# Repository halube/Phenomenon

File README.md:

# Phenomenon - Low-cost and multi-sensor system for automated phenotyping of plant in vitro culture
This is the official code implementation and used hardware of our paper, which is currently under a journal review:

The main mechanical components of the system were:
- OpenBuilds ACRO 1515 60" x 60" (XY gantry)
- Openbuilds Linear Actuator (Z axis)

Network connection & embedded system:
- Router & PoE-Switch
- 2 x Raspberry Pi 4B & PoE-Shield
- 2 x Wemos D1 Mini

Sensors of the system:
- RGB Raspberry Pi Camera High quality 12 MB with Edmund Optics 6mm low distortion lens equipied
- Thermal PureThermal 2 & Lepton 3.5
- Spectral µSpectrometer Hamamatsu C12880MA
- Depth Laser distance sensor OD-Mini OB1-B100

Hardware
- Containing 3D printable parts and PCB-Layouts

Software
- Containing Dockerfiles and Python scripts

Cite:
Bethge H, Winkelmann T, Lüdeke P, Rath T. Low-cost and automated phenotyping system “Phenomenon” for multi-sensor in situ monitoring in plant in vitro culture. Plant methods. 2023 May 2;19(1):42.

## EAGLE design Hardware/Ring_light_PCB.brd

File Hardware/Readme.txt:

Some of the 3D printed parts for cable chain were inspired by the build of "hilleke" & "dragonfire81m" 
(Thingiverse-User: https://www.thingiverse.com/thing:3110642; https://www.thingiverse.com/thing:2780302) but mainly also modified.

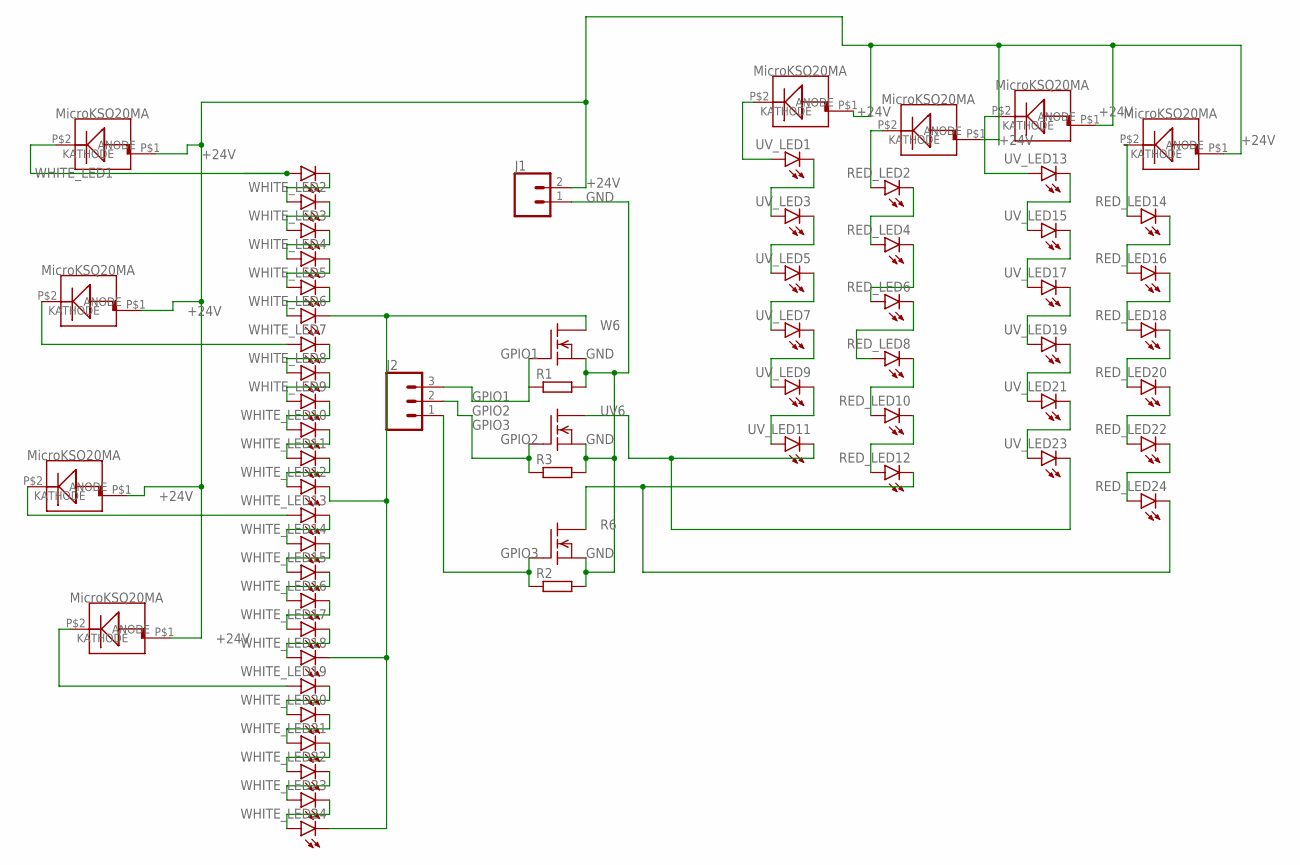
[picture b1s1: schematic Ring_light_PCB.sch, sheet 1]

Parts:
J1: CONN_025MM; SCREWTERMINAL-5MM-2
J2: CONN_03-SCREW-5MM; SCREWTERMINAL-5MM-3
Q1, Q2, Q4: BUZ10; TO220
R1, R2, R3: R-EU_0204/7; 0204/7
RED_LED2, RED_LED4, RED_LED6, RED_LED8, RED_LED10, RED_LED12, RED_LED14, RED_LED16, RED_LED18, RED_LED20, RED_LED22, RED_LED24: LED5MM
U$1, U$2, U$3, U$4, U$5, U$6, U$7, U$8: MICROKSQ220MA; MICROKSQ20MA
UV_LED1, UV_LED3, UV_LED5, UV_LED7, UV_LED9, UV_LED11, UV_LED13, UV_LED15, UV_LED17, UV_LED19, UV_LED21, UV_LED23: LED5MM
WHITE_LED1, WHITE_LED2, WHITE_LED3, WHITE_LED4, WHITE_LED5, WHITE_LED6, WHITE_LED7, WHITE_LED8, WHITE_LED9, WHITE_LED10, WHITE_LED11, WHITE_LED12, WHITE_LED13, WHITE_LED14, WHITE_LED15, WHITE_LED16, WHITE_LED17, WHITE_LED18, WHITE_LED19, WHITE_LED20, WHITE_LED21, WHITE_LED22, WHITE_LED23, WHITE_LED24: LED5MM

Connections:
+24V: J1.2, U$1.P$1 (KATHODE), U$2.P$1 (KATHODE), U$3.P$1 (KATHODE), U$4.P$1 (KATHODE), U$5.P$1 (KATHODE), U$6.P$1 (KATHODE), U$7.P$1 (KATHODE), U$8.P$1 (KATHODE)
GND: J1.1, Q1.3 (S), Q2.3 (S), Q4.3 (S), R1.2, R2.2, R3.2
GPIO1: J2.3, Q1.1 (G), R1.1
GPIO2: J2.2, Q2.1 (G), R3.1
GPIO3: J2.1, Q4.1 (G), R2.1
R0: RED_LED2.A, U$8.P$2 (ANODE)
R1: RED_LED2.K (C), RED_LED4.A
R2: RED_LED4.K (C), RED_LED6.A
R3: RED_LED6.K (C), RED_LED8.A
R4: RED_LED8.K (C), RED_LED10.A
R5: RED_LED10.K (C), RED_LED12.A
R6: Q4.2 (D), RED_LED12.K (C), RED_LED24.K (C)
R7: RED_LED14.A, U$6.P$2 (ANODE)
R8: RED_LED14.K (C), RED_LED16.A
R9: RED_LED16.K (C), RED_LED18.A
R10: RED_LED18.K (C), RED_LED20.A
R11: RED_LED20.K (C), RED_LED22.A
R12: RED_LED22.K (C), RED_LED24.A
UV0: U$7.P$2 (ANODE), UV_LED1.A
UV1: UV_LED1.K (C), UV_LED3.A
UV2: UV_LED3.K (C), UV_LED5.A
UV3: UV_LED5.K (C), UV_LED7.A
UV4: UV_LED7.K (C), UV_LED9.A
UV5: UV_LED9.K (C), UV_LED11.A
UV6: Q2.2 (D), UV_LED11.K (C), UV_LED23.K (C)
UV7: U$5.P$2 (ANODE), UV_LED13.A
UV8: UV_LED13.K (C), UV_LED15.A
UV9: UV_LED15.K (C), UV_LED17.A
UV10: UV_LED17.K (C), UV_LED19.A
UV11: UV_LED19.K (C), UV_LED21.A
UV12: UV_LED21.K (C), UV_LED23.A
W0: U$1.P$2 (ANODE), WHITE_LED1.A
W1: WHITE_LED1.K (C), WHITE_LED2.A
W2: WHITE_LED2.K (C), WHITE_LED3.A
W3: WHITE_LED3.K (C), WHITE_LED4.A
W4: WHITE_LED4.K (C), WHITE_LED5.A
W5: WHITE_LED5.K (C), WHITE_LED6.A
W6: Q1.2 (D), WHITE_LED6.K (C), WHITE_LED12.K (C), WHITE_LED18.K (C), WHITE_LED24.K (C)
W7: U$2.P$2 (ANODE), WHITE_LED7.A
W8: WHITE_LED7.K (C), WHITE_LED8.A
W9: WHITE_LED8.K (C), WHITE_LED9.A
W10: WHITE_LED9.K (C), WHITE_LED10.A
W11: WHITE_LED10.K (C), WHITE_LED11.A
W12: WHITE_LED11.K (C), WHITE_LED12.A
W13: U$3.P$2 (ANODE), WHITE_LED13.A
W14: WHITE_LED13.K (C), WHITE_LED14.A
W15: WHITE_LED14.K (C), WHITE_LED15.A
W16: WHITE_LED15.K (C), WHITE_LED16.A
W17: WHITE_LED16.K (C), WHITE_LED17.A
W18: WHITE_LED17.K (C), WHITE_LED18.A
W19: U$4.P$2 (ANODE), WHITE_LED19.A
W20: WHITE_LED19.K (C), WHITE_LED20.A
W21: WHITE_LED20.K (C), WHITE_LED21.A
W22: WHITE_LED21.K (C), WHITE_LED22.A
W23: WHITE_LED22.K (C), WHITE_LED23.A
W24: WHITE_LED23.K (C), WHITE_LED24.A

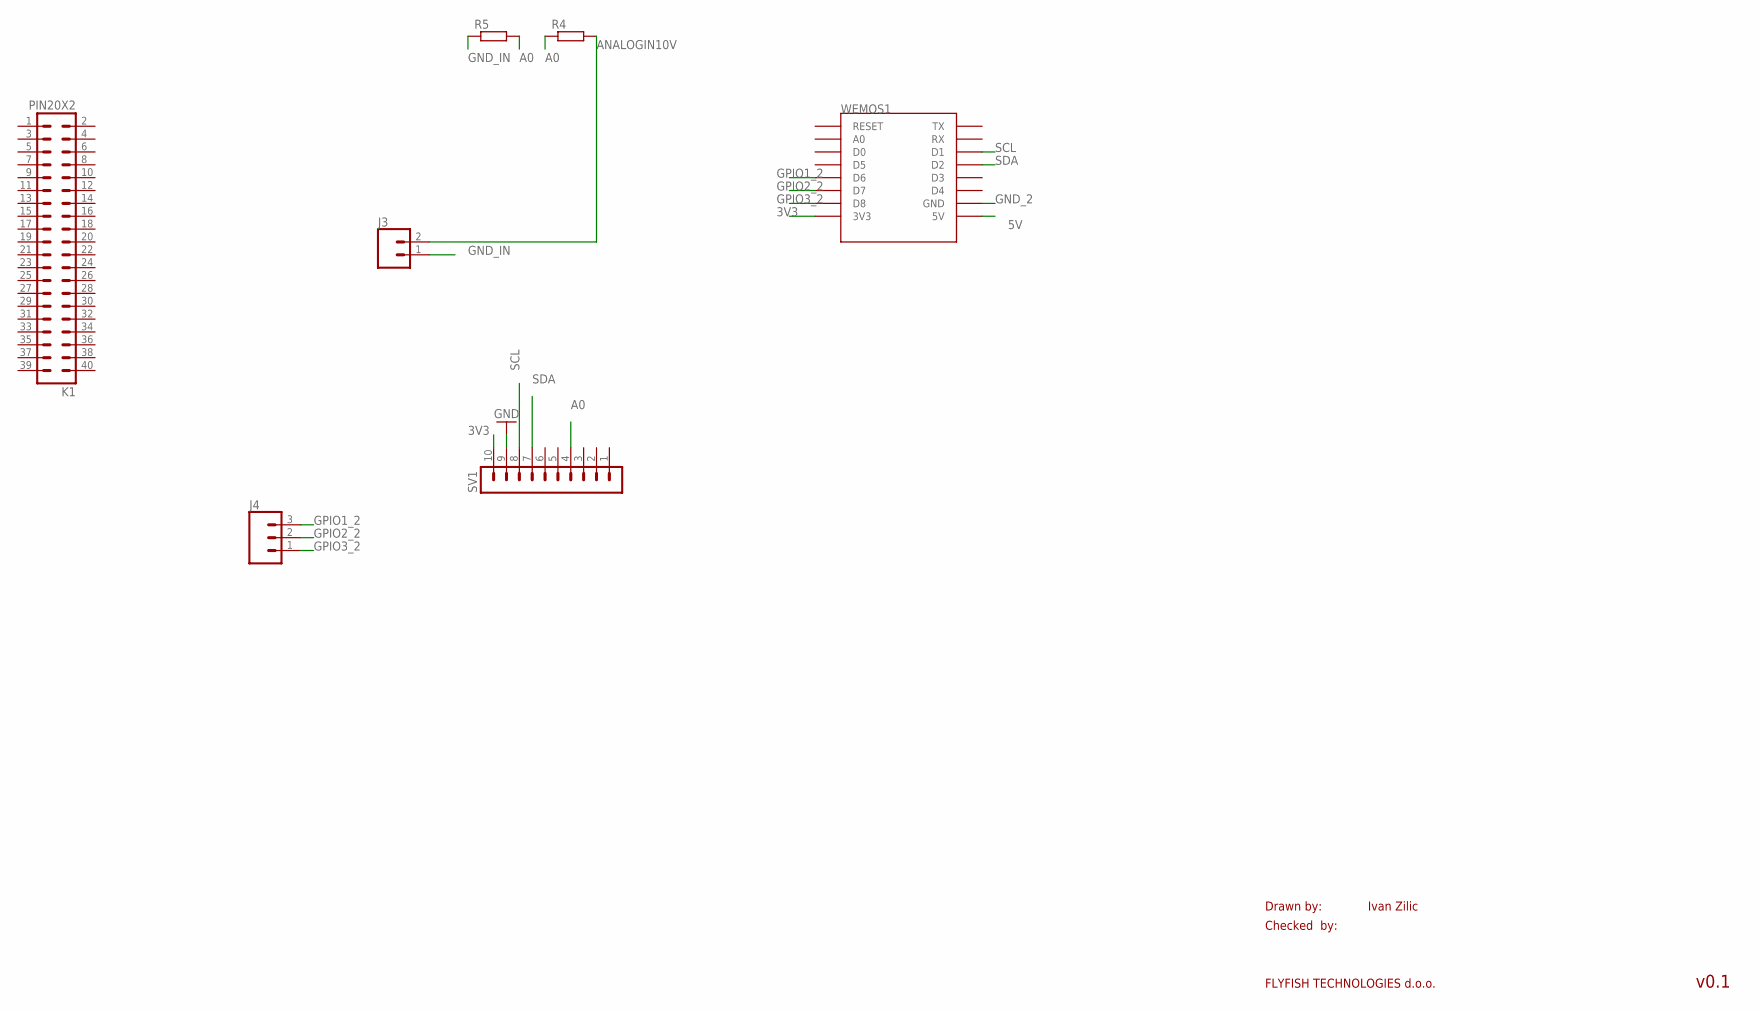
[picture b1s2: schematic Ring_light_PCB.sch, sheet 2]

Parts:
J3: CONN_025MM; SCREWTERMINAL-5MM-2
J4: CONN_03-SCREW-5MM; SCREWTERMINAL-5MM-3
K1: PIN20X2; PIN_20X2
R4, R5: R-EU_0204/7; 0204/7
SV1: MA10-1
WEMOS1: WEMOS-D1-MINI

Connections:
3V3: SV1.10, WEMOS1.3V3
5V: WEMOS1.5V
A0: R4.1, R5.2, SV1.4
ANALOGIN10V: J3.2, R4.2
GND_2: SV1.9, WEMOS1.GND
GND_IN: J3.1, R5.1
GPIO1_2: J4.3, WEMOS1.D6
GPIO2_2: J4.2, WEMOS1.D7
GPIO3_2: J4.1, WEMOS1.D8
SCL: SV1.8, WEMOS1.D1
SDA: SV1.7, WEMOS1.D2

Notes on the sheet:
Drawn by:
Checked by:
FLYFISH TECHNOLOGIES d.o.o.
Ivan Zilic
v0.1

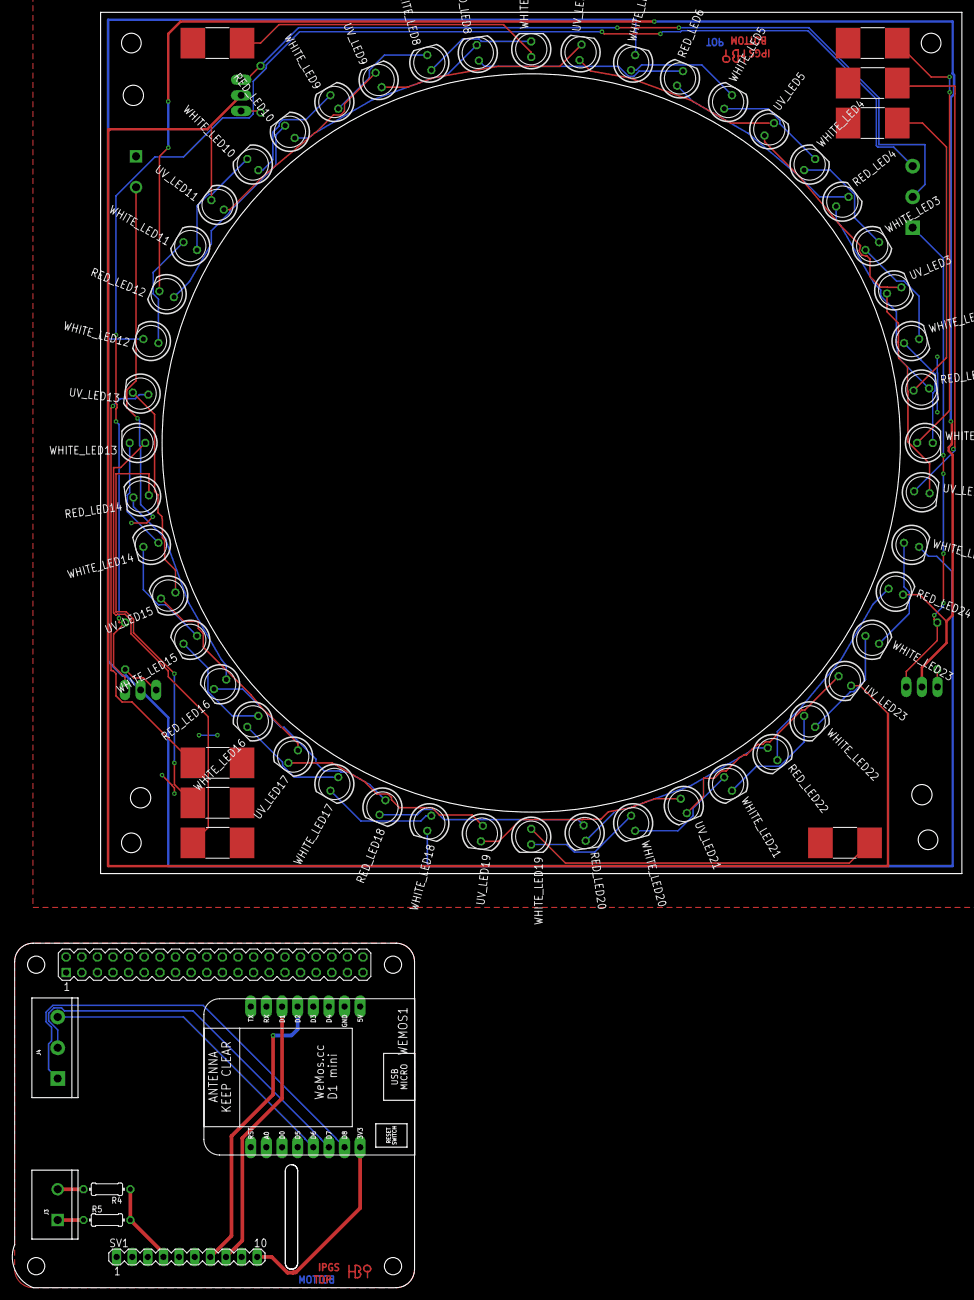
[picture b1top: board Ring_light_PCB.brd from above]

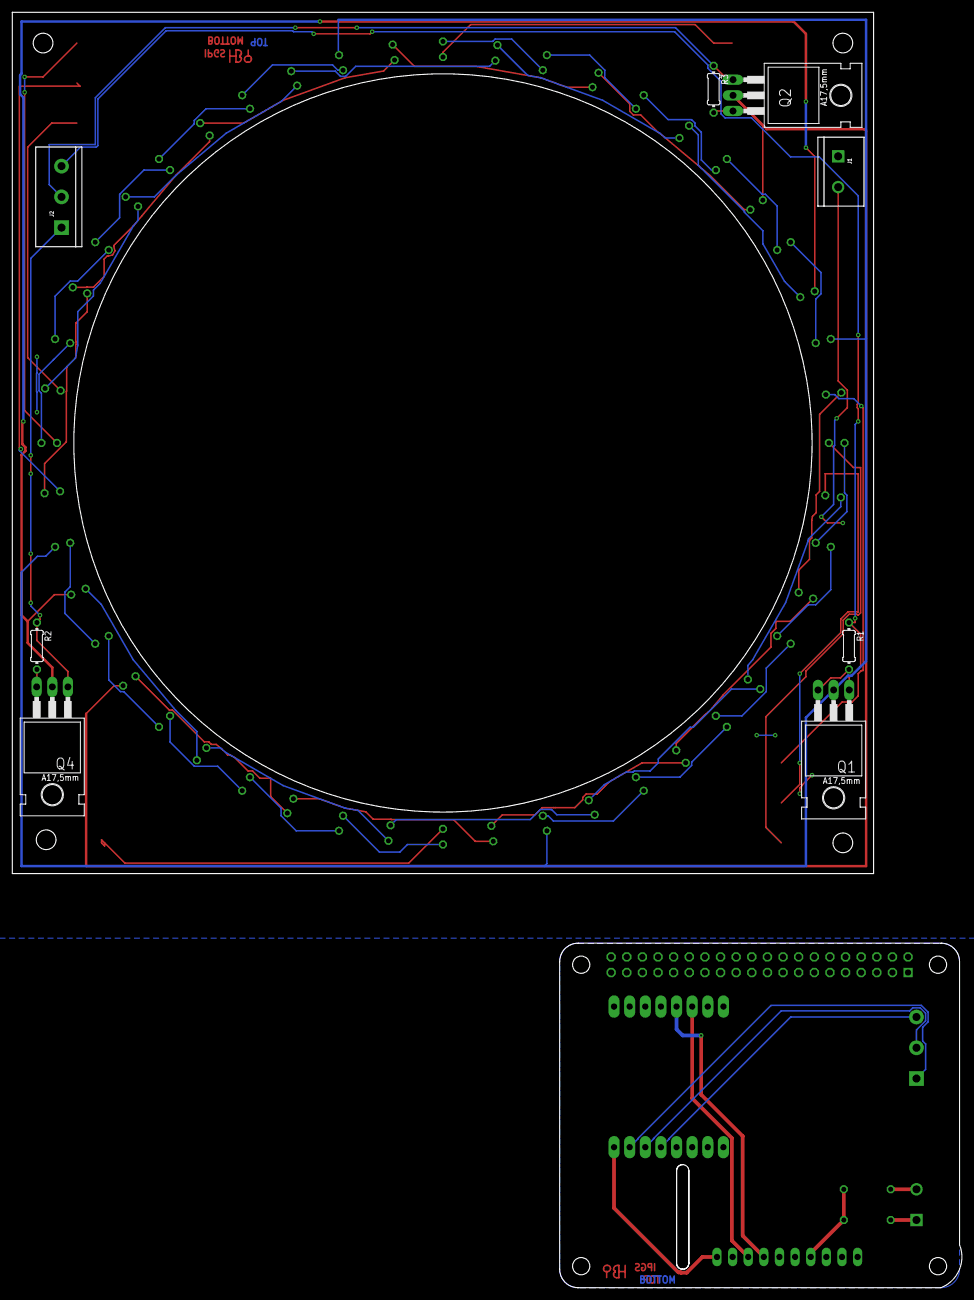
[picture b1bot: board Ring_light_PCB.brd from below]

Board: 2 copper layers, 154.2 x 207.2 mm, 71 parts (8 on the bottom side), 66 nets.

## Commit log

2025-02-12 Rename Fig.14 M - Software desgin.png to Fig.14.png

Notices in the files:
parts and their libraries:
SparkFun-Connectors: Licensing: Creative Commons ShareAlike 4.0 International - https://creativecommons.org/licenses/by-sa/4.0
